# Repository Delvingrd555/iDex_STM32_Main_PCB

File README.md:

# iDex_STM32_Main_PCB
Main PCB Designs and Circuits Only

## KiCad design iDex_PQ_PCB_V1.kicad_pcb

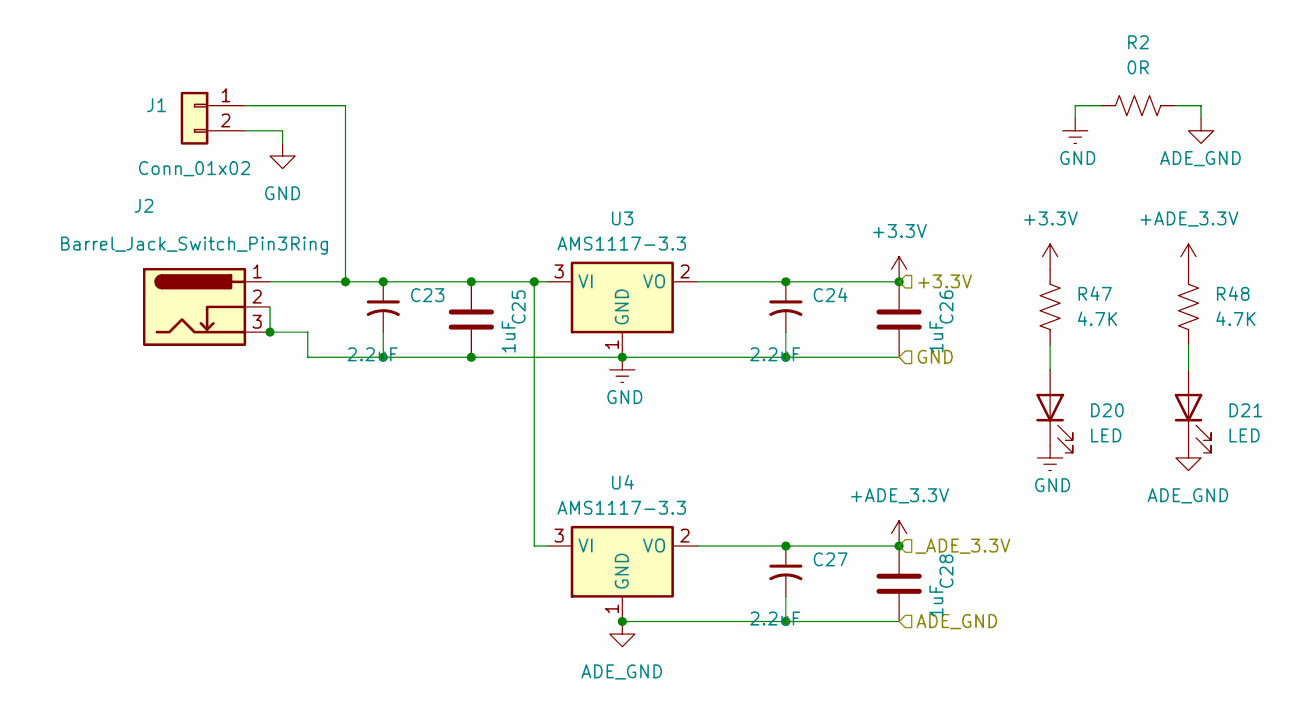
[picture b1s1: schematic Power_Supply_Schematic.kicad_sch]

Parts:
C23, C24, C27: 2.2uF; C_Radial_D10.0mm_H12.5mm_P5.00mm
C25, C26, C28: 1uF; C_1206_3216Metric_Pad1.33x1.80mm_HandSolder
D20, D21: LED; LED_0805_2012Metric_Pad1.15x1.40mm_HandSolder
J1: Conn_01x02; Altech_AK100_1x02_P5.00mm
J2: Barrel_Jack_Switch_Pin3Ring; BarrelJack_Horizontal
R2: 0R; R_0805_2012Metric_Pad1.20x1.40mm_HandSolder
R47, R48: 4.7K; R_0805_2012Metric_Pad1.20x1.40mm_HandSolder
U3, U4: AMS1117-3.3; SOT-223-3_TabPin2

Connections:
+3.3V: C24.1, C26.2, R47.2, U3.2 (VO); also elsewhere on the board
+ADE_3.3V: C27.1, C28.2, R48.2, U4.2 (VO); also elsewhere on the board
ADE_GND: C27.2, C28.1, D21.1 (K), R2.2, U4.1 (GND); also elsewhere on the board
GND: C23.2, C24.2, C25.1, C26.1, D20.1 (K), J1.2, J2.2, J2.3, R2.1, U3.1 (GND); also elsewhere on the board
unnamed: D20.2 (A), R47.1
unnamed: D21.2 (A), R48.1
unnamed: C23.1, C25.2, J1.1, J2.1, U3.3 (VI), U4.3 (VI)

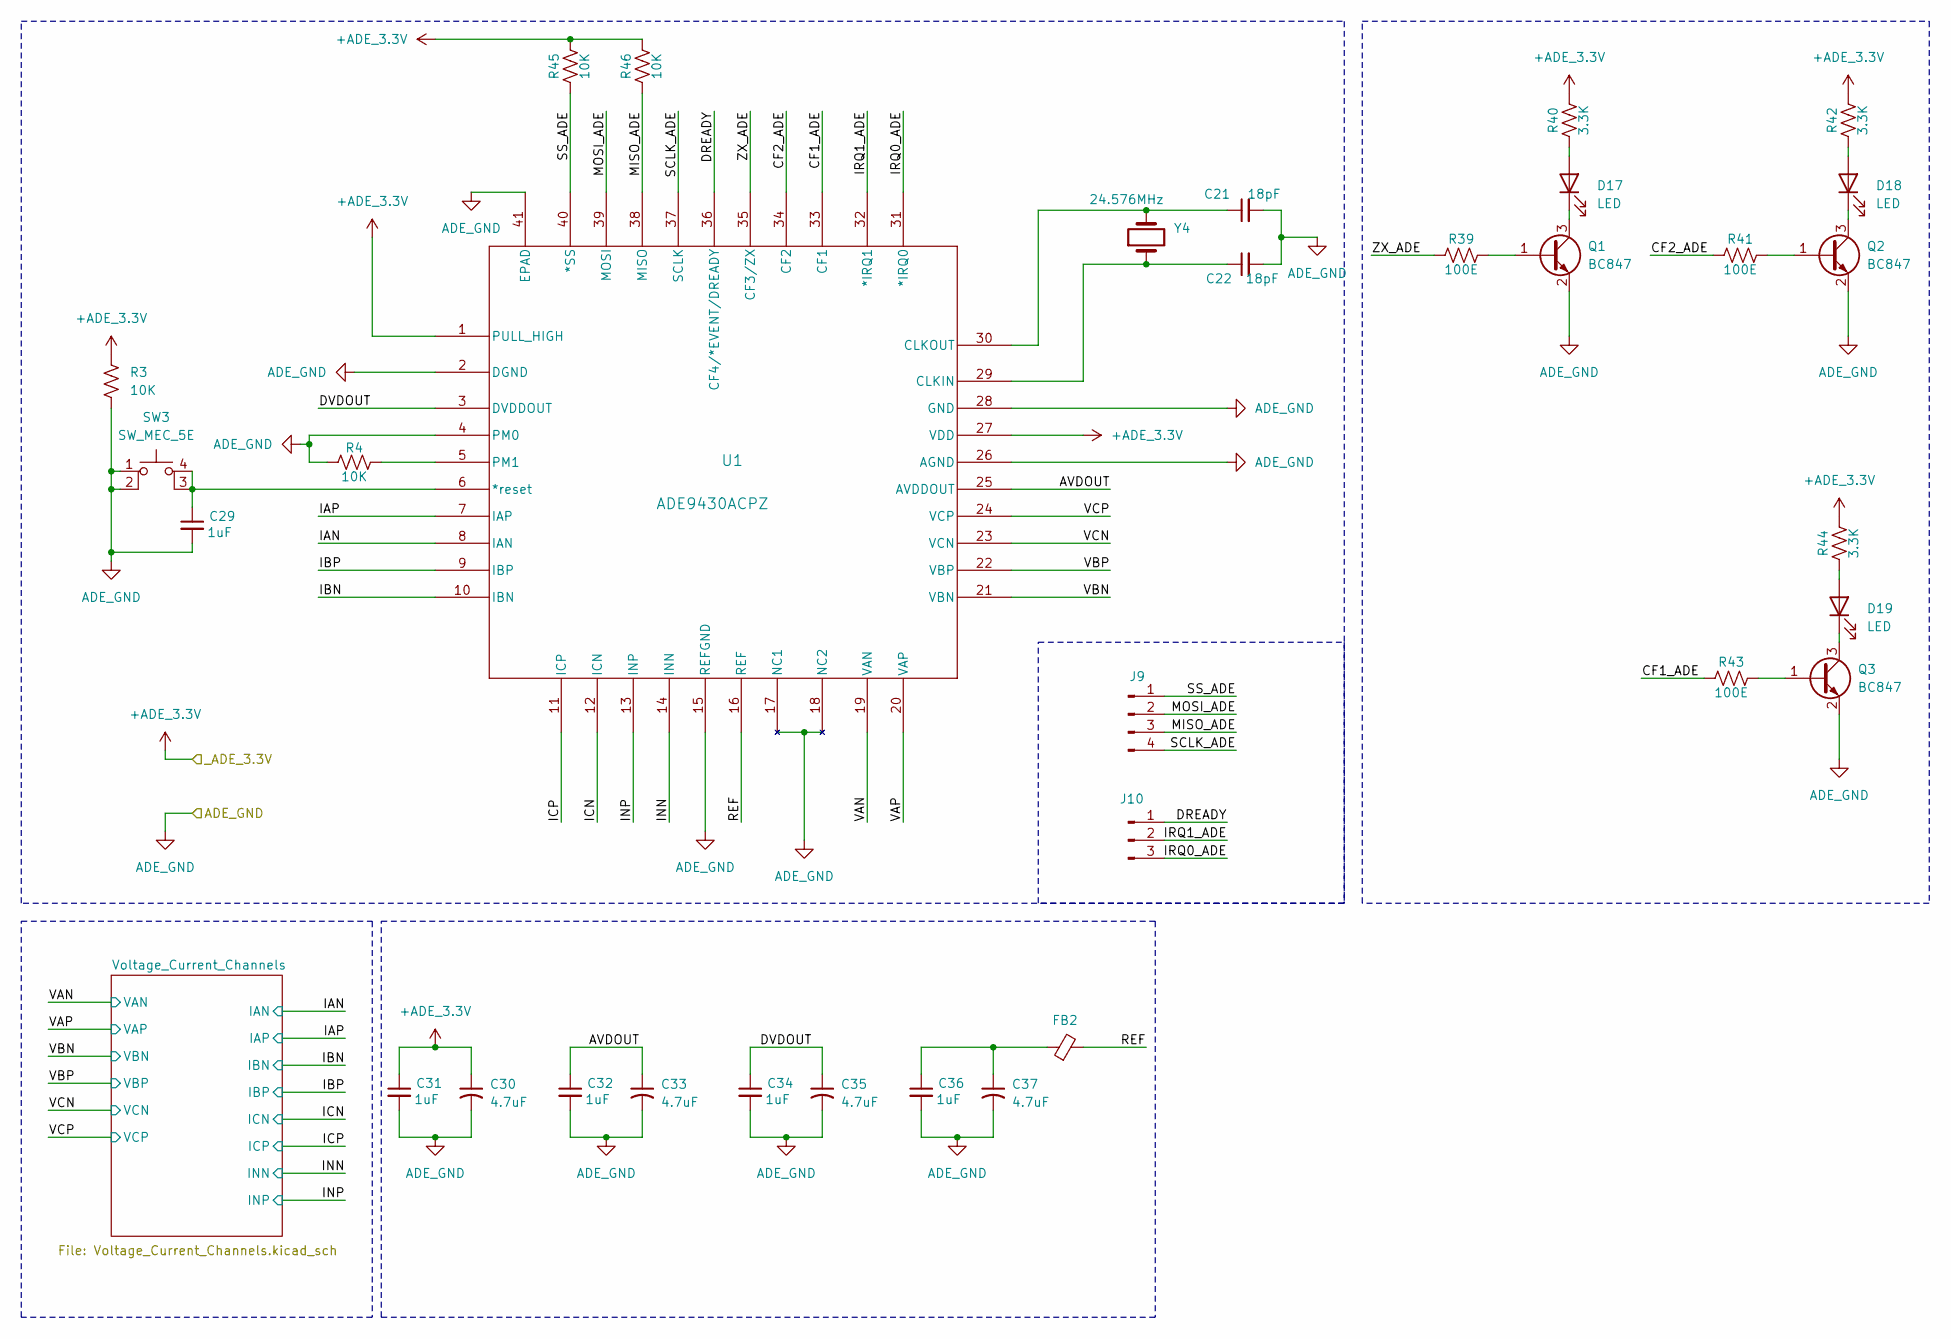
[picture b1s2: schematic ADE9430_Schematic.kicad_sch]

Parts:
C21, C22: 18pF; C_0805_2012Metric_Pad1.18x1.45mm_HandSolder
C29, C31, C32, C34, C36: 1uF; C_0805_2012Metric_Pad1.18x1.45mm_HandSolder
C30, C33, C35, C37: 4.7uF; C_Radial_D6.3mm_H5.0mm_P2.50mm
D17, D18, D19: LED; LED_D3.0mm
FB2: FerriteBead_Small; C_1206_3216Metric
J9: Conn; PinHeader_1x04_P2.54mm_Vertical
J10: Conn_01x03_Pin; PinHeader_1x03_P2.54mm_Vertical
Q1, Q2, Q3: BC847; SOT-23
R3, R4, R45, R46: 10K; R_0805_2012Metric_Pad1.20x1.40mm_HandSolder
R39, R41, R43: 100E; R_0805_2012Metric_Pad1.20x1.40mm_HandSolder
R40, R42, R44: 3.3K; R_0805_2012Metric_Pad1.20x1.40mm_HandSolder
SW3: SW_MEC_5E; SW_Push_2P1T_Toggle_CK_PVA1xxH1xxxxxxV2
U1: ADE9430ACPZ; ADE9430ACPZ_ADI
Y4: 24.576MHz; Crystal_HC50_Vertical

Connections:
+ADE_3.3V: C30.1, C31.1, R3.1, R40.2, R42.2, R44.2, R45.2, R46.2, U1.1 (PULL_HIGH), U1.27 (VDD); also elsewhere on the board
/ADE9430_Schematic/AVDOUT: C32.1, C33.1, U1.25 (AVDDOUT)
/ADE9430_Schematic/CF1_ADE: R43.1, U1.33 (CF1)
/ADE9430_Schematic/CF2_ADE: R41.1, U1.34 (CF2)
/ADE9430_Schematic/DREADY: J10.1, U1.36 (CF4/*EVENT/DREADY)
/ADE9430_Schematic/DVDOUT: C34.1, C35.1, U1.3 (DVDDOUT)
/ADE9430_Schematic/IAN: U1.8 (IAN); also elsewhere on the board
/ADE9430_Schematic/IAP: U1.7 (IAP); also elsewhere on the board
/ADE9430_Schematic/IBN: U1.10 (IBN); also elsewhere on the board
/ADE9430_Schematic/IBP: U1.9 (IBP); also elsewhere on the board
/ADE9430_Schematic/ICN: U1.12 (ICN); also elsewhere on the board
/ADE9430_Schematic/ICP: U1.11 (ICP); also elsewhere on the board
/ADE9430_Schematic/INN: U1.14 (INN); also elsewhere on the board
/ADE9430_Schematic/INP: U1.13 (INP); also elsewhere on the board
/ADE9430_Schematic/IRQ0_ADE: J10.3, U1.31 (*IRQ0)
/ADE9430_Schematic/IRQ1_ADE: J10.2, U1.32 (*IRQ1)
/ADE9430_Schematic/MISO_ADE: J9.3, R46.1, U1.38 (MISO)
/ADE9430_Schematic/MOSI_ADE: J9.2, U1.39 (MOSI)
/ADE9430_Schematic/REF: FB2.2, U1.16 (REF)
/ADE9430_Schematic/SCLK_ADE: J9.4, U1.37 (SCLK)
/ADE9430_Schematic/SS_ADE: J9.1, R45.1, U1.40 (*SS)
/ADE9430_Schematic/VAN: U1.19 (VAN); also elsewhere on the board
/ADE9430_Schematic/VAP: U1.20 (VAP); also elsewhere on the board
/ADE9430_Schematic/VBN: U1.21 (VBN); also elsewhere on the board
/ADE9430_Schematic/VBP: U1.22 (VBP); also elsewhere on the board
/ADE9430_Schematic/VCN: U1.23 (VCN); also elsewhere on the board
/ADE9430_Schematic/VCP: U1.24 (VCP); also elsewhere on the board
/ADE9430_Schematic/ZX_ADE: R39.1, U1.35 (CF3/ZX)
ADE_GND: C21.2, C22.2, C29.2, C30.2, C31.2, C32.2, C33.2, C34.2, C35.2, C36.2, C37.2, Q1.2 (E), Q2.2 (E), Q3.2 (E), R3.2, R4.1, SW3.1, SW3.2, U1.2 (DGND), U1.4 (PM0), U1.15 (REFGND), U1.17 (NC1), U1.18 (NC2), U1.26 (AGND), U1.28 (GND), U1.41 (EPAD); also elsewhere on the board
unnamed: C36.1, C37.1, FB2.1
unnamed: D17.2 (A), R40.1
unnamed: D17.1 (K), Q1.3 (C)
unnamed: D18.2 (A), R42.1
unnamed: D18.1 (K), Q2.3 (C)
unnamed: D19.2 (A), R44.1
unnamed: D19.1 (K), Q3.3 (C)
unnamed: Q1.1 (B), R39.2
unnamed: Q2.1 (B), R41.2
unnamed: Q3.1 (B), R43.2
unnamed: C29.1, SW3.3 (K), SW3.4 (A), U1.6 (*reset)
unnamed: C22.1, U1.29 (CLKIN), Y4.1
unnamed: C21.1, U1.30 (CLKOUT), Y4.2
unnamed: R4.2, U1.5 (PM1)

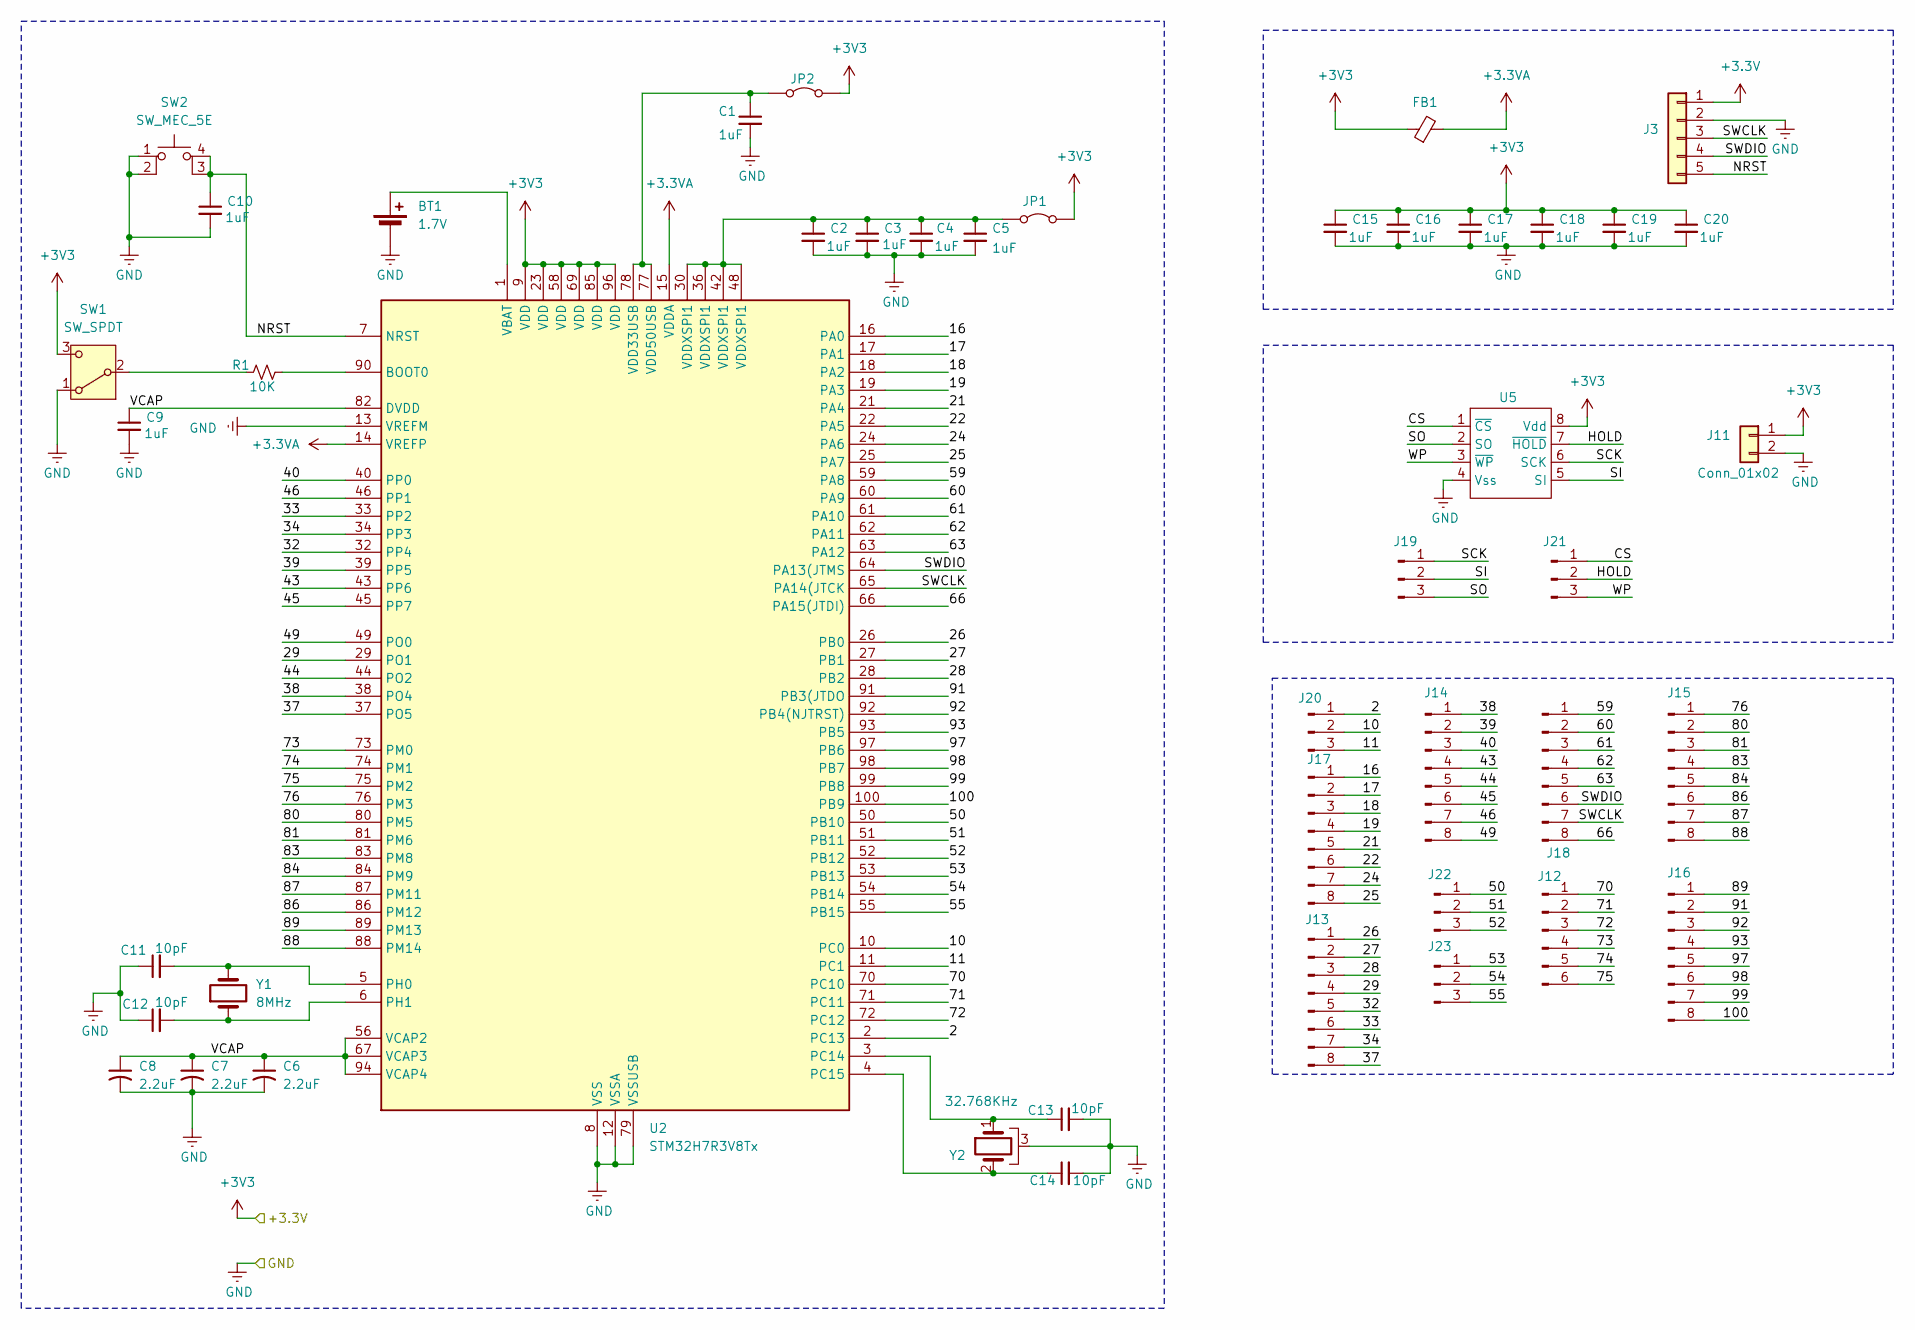
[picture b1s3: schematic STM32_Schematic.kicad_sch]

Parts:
BT1: 1.7V; BatteryHolder_MYOUNG_BS-07-A1BJ001_CR2032
C1, C2, C3, C4, C5, C9, C10, C15, C16, C17, C18, C19, C20: 1uF; C_0805_2012Metric_Pad1.18x1.45mm_HandSolder
C6, C7, C8: 2.2uF; C_Radial_D6.3mm_H5.0mm_P2.50mm
C11, C12, C13, C14: 10pF; C_0805_2012Metric_Pad1.18x1.45mm_HandSolder
FB1: FerriteBead_Small; C_1206_3216Metric
J3: Conn_01x05; TerminalBlock_Phoenix_MPT-0,5-5-2.54_1x05_P2.54mm_Horizontal
J11: Conn_01x02; PinSocket_1x02_P2.54mm_Vertical
J12: Conn_01x06_Pin; PinHeader_1x06_P2.54mm_Vertical
J13, J14, J15, J16, J17, J18: Conn_01x08_Pin; PinSocket_1x08_P2.54mm_Vertical
J19, J20, J21, J22, J23: Conn_01x03_Pin; PinHeader_1x03_P2.54mm_Vertical
JP1, JP2: Jumper_2_Bridged; PinHeader_1x02_P2.54mm_Vertical
R1: 10K; R_0805_2012Metric_Pad1.20x1.40mm_HandSolder
SW1: SW_SPDT; PinHeader_1x03_P2.54mm_Vertical
SW2: SW_MEC_5E; SW_Push_2P1T_Toggle_CK_PVA1xxH1xxxxxxV2
U2: STM32H7R3V8Tx; LQFP-100_14x14mm_P0.5mm
U5: SOIC-8_3.9x4.9mm_P1.27mm
Y1: 8MHz; Crystal_HC50_Vertical
Y2: 32.768KHz; Crystal_DS26_D2.0mm_L6.0mm_Horizontal_1EP_style1

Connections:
+3.3V: C15.1, C16.1, C17.1, C18.1, C19.1, C20.1, FB1.1, J3.1, J11.1, JP1.2 (B), JP2.2 (B), SW1.3 (C), U2.9 (VDD), U2.23 (VDD), U2.58 (VDD), U2.69 (VDD), U2.85 (VDD), U2.96 (VDD), U5.8 (Vdd); also elsewhere on the board
+3.3VA: FB1.2, U2.14 (VREFP), U2.15 (VDDA)
/STM32_Schematic/2: J20.1, U2.2 (PC13)
/STM32_Schematic/10: J20.2, U2.10 (PC0)
/STM32_Schematic/11: J20.3, U2.11 (PC1)
/STM32_Schematic/16: J17.1, U2.16 (PA0)
/STM32_Schematic/17: J17.2, U2.17 (PA1)
/STM32_Schematic/18: J17.3, U2.18 (PA2)
/STM32_Schematic/19: J17.4, U2.19 (PA3)
/STM32_Schematic/21: J17.5, U2.21 (PA4)
/STM32_Schematic/22: J17.6, U2.22 (PA5)
/STM32_Schematic/24: J17.7, U2.24 (PA6)
/STM32_Schematic/25: J17.8, U2.25 (PA7)
/STM32_Schematic/26: J13.1, U2.26 (PB0)
/STM32_Schematic/27: J13.2, U2.27 (PB1)
/STM32_Schematic/28: J13.3, U2.28 (PB2)
/STM32_Schematic/29: J13.4, U2.29 (PO1)
/STM32_Schematic/32: J13.5, U2.32 (PP4)
/STM32_Schematic/33: J13.6, U2.33 (PP2)
/STM32_Schematic/34: J13.7, U2.34 (PP3)
/STM32_Schematic/37: J13.8, U2.37 (PO5)
/STM32_Schematic/38: J14.1, U2.38 (PO4)
/STM32_Schematic/39: J14.2, U2.39 (PP5)
/STM32_Schematic/40: J14.3, U2.40 (PP0)
/STM32_Schematic/43: J14.4, U2.43 (PP6)
/STM32_Schematic/44: J14.5, U2.44 (PO2)
/STM32_Schematic/45: J14.6, U2.45 (PP7)
/STM32_Schematic/46: J14.7, U2.46 (PP1)
/STM32_Schematic/49: J14.8, U2.49 (PO0)
/STM32_Schematic/50: J22.1, U2.50 (PB10)
/STM32_Schematic/51: J22.2, U2.51 (PB11)
/STM32_Schematic/52: J22.3, U2.52 (PB12)
/STM32_Schematic/53: J23.1, U2.53 (PB13)
/STM32_Schematic/54: J23.2, U2.54 (PB14)
/STM32_Schematic/55: J23.3, U2.55 (PB15)
/STM32_Schematic/59: J18.1, U2.59 (PA8)
/STM32_Schematic/60: J18.2, U2.60 (PA9)
/STM32_Schematic/61: J18.3, U2.61 (PA10)
/STM32_Schematic/62: J18.4, U2.62 (PA11)
/STM32_Schematic/63: J18.5, U2.63 (PA12)
/STM32_Schematic/66: J18.8, U2.66 (PA15(JTDI))
/STM32_Schematic/70: J12.1, U2.70 (PC10)
/STM32_Schematic/71: J12.2, U2.71 (PC11)
/STM32_Schematic/72: J12.3, U2.72 (PC12)
/STM32_Schematic/73: J12.4, U2.73 (PM0)
/STM32_Schematic/74: J12.5, U2.74 (PM1)
/STM32_Schematic/75: J12.6, U2.75 (PM2)
/STM32_Schematic/76: J15.1, U2.76 (PM3)
/STM32_Schematic/80: J15.2, U2.80 (PM5)
/STM32_Schematic/81: J15.3, U2.81 (PM6)
/STM32_Schematic/83: J15.4, U2.83 (PM8)
/STM32_Schematic/84: J15.5, U2.84 (PM9)
/STM32_Schematic/86: J15.6, U2.86 (PM12)
/STM32_Schematic/87: J15.7, U2.87 (PM11)
/STM32_Schematic/88: J15.8, U2.88 (PM14)
/STM32_Schematic/89: J16.1, U2.89 (PM13)
/STM32_Schematic/91: J16.2, U2.91 (PB3(JTDO)
/STM32_Schematic/92: J16.3, U2.92 (PB4(NJTRST))
/STM32_Schematic/93: J16.4, U2.93 (PB5)
/STM32_Schematic/97: J16.5, U2.97 (PB6)
/STM32_Schematic/98: J16.6, U2.98 (PB7)
/STM32_Schematic/99: J16.7, U2.99 (PB8)
/STM32_Schematic/100: J16.8, U2.100 (PB9)
/STM32_Schematic/CS: J21.1, U5.1 (~CS)
/STM32_Schematic/HOLD: J21.2, U5.7 (~HOLD)
/STM32_Schematic/NRST: C10.1, J3.5, SW2.3 (K), SW2.4 (A), U2.7 (NRST)
/STM32_Schematic/SCK: J19.1, U5.6 (SCK)
/STM32_Schematic/SI: J19.2, U5.5 (SI)
/STM32_Schematic/SO: J19.3, U5.2 (SO)
/STM32_Schematic/SWCLK: J3.3, J18.7, U2.65 (PA14(JTCK)
/STM32_Schematic/SWDIO: J3.4, J18.6, U2.64 (PA13(JTMS)
/STM32_Schematic/VCAP: C6.1, C7.1, C8.1, C9.1, U2.56 (VCAP2), U2.67 (VCAP3), U2.82 (DVDD), U2.94 (VCAP4)
/STM32_Schematic/WP: J21.3, U5.3 (~WP)
GND: BT1.2 (-), C1.2, C2.2, C3.2, C4.2, C5.2, C6.2, C7.2, C8.2, C9.2, C10.2, C11.1, C12.1, C13.2, C14.2, C15.2, C16.2, C17.2, C18.2, C19.2, C20.2, J3.2, J11.2, SW1.1 (A), SW2.1, SW2.2, U2.8 (VSS), U2.12 (VSSA), U2.13 (VREFM), U2.20 (VSS), U2.31 (VSS), U2.35 (VSS), U2.41 (VSS), U2.47 (VSS), U2.57 (VSS), U2.68 (VSS), U2.79 (VSSUSB), U2.95 (VSS), U5.4 (Vss), Y2.3; also elsewhere on the board
unnamed: BT1.1 (+), U2.1 (VBAT)
unnamed: C2.1, C3.1, C4.1, C5.1, JP1.1 (A), U2.30 (VDDXSPI1), U2.36 (VDDXSPI1), U2.42 (VDDXSPI1), U2.48 (VDDXSPI1)
unnamed: C1.1, JP2.1 (A), U2.77 (VDD50USB), U2.78 (VDD33USB)
unnamed: R1.1, SW1.2 (B)
unnamed: R1.2, U2.90 (BOOT0)
unnamed: C13.1, U2.3 (PC14), Y2.1
unnamed: C14.1, U2.4 (PC15), Y2.2
unnamed: C11.2, U2.5 (PH0), Y1.2
unnamed: C12.2, U2.6 (PH1), Y1.1

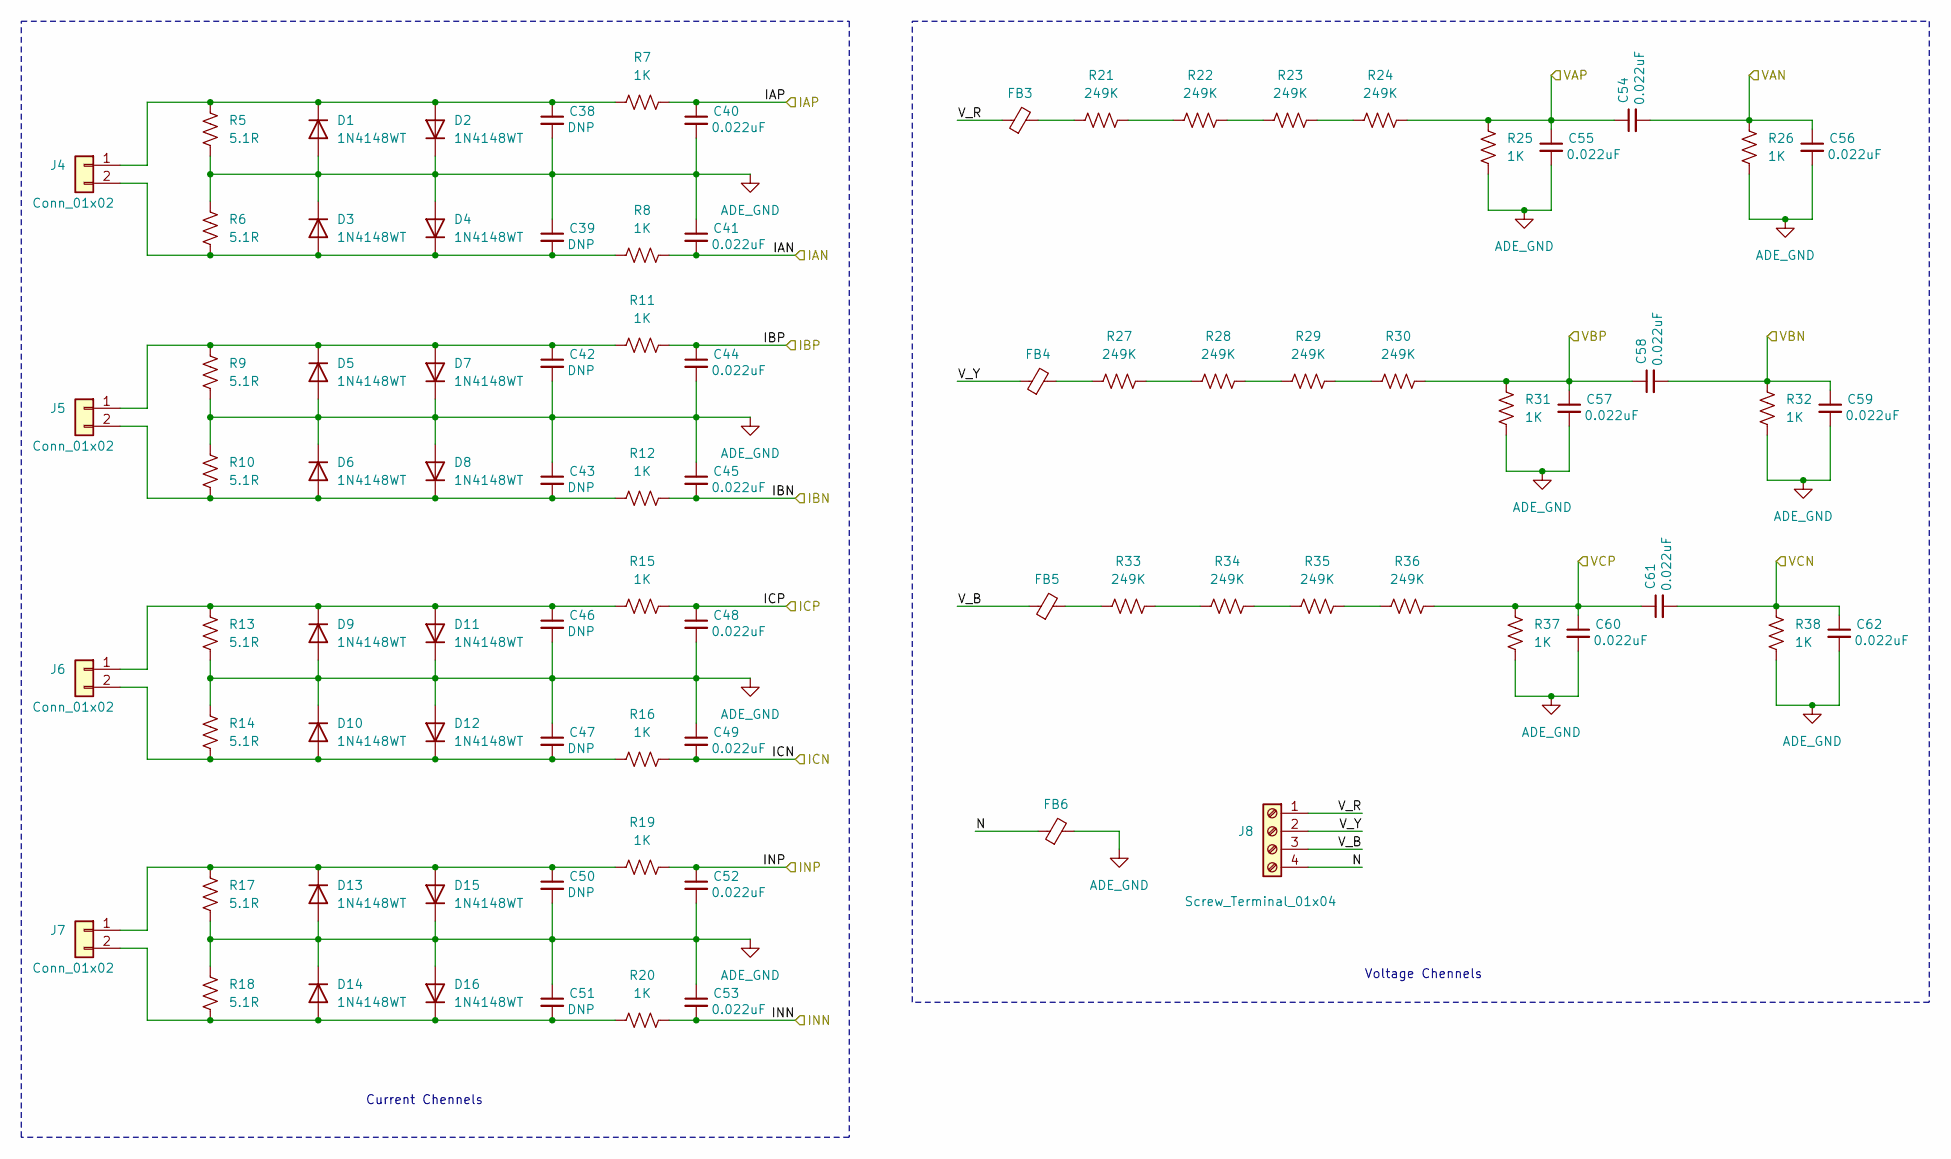
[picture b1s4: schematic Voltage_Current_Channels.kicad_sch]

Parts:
C38, C39, C42, C43, C46, C47, C50, C51: DNP; C_0805_2012Metric_Pad1.18x1.45mm_HandSolder
C40, C41, C44, C45, C48, C49, C52, C53, C54, C55, C56, C57, C58, C59, C60, C61, C62: 0.022uF; C_0805_2012Metric_Pad1.18x1.45mm_HandSolder
D1, D2, D3, D4, D5, D6, D7, D8, D9, D10, D11, D12, D13, D14, D15, D16: 1N4148WT; D_SOD-523
FB3, FB4, FB5, FB6: FerriteBead_Small; C_1206_3216Metric
J4, J5, J6, J7: Conn_01x02; PinSocket_1x02_P2.54mm_Vertical
J8: Screw_Terminal_01x04; TerminalBlock_MaiXu_MX126-5.0-04P_1x04_P5.00mm
R5, R6, R9, R10, R13, R14, R17, R18: 5.1R; R_0805_2012Metric_Pad1.20x1.40mm_HandSolder
R7, R8, R11, R12, R15, R16, R19, R20, R25, R26, R31, R32, R37, R38: 1K; R_0805_2012Metric_Pad1.20x1.40mm_HandSolder
R21, R22, R23, R24, R27, R28, R29, R30, R33, R34, R35, R36: 249K; R_0805_2012Metric_Pad1.20x1.40mm_HandSolder

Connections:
/ADE9430_Schematic/IAN: C41.2, R8.2; also elsewhere on the board
/ADE9430_Schematic/IAP: C40.1, R7.2; also elsewhere on the board
/ADE9430_Schematic/IBN: C45.2, R12.2; also elsewhere on the board
/ADE9430_Schematic/IBP: C44.1, R11.2; also elsewhere on the board
/ADE9430_Schematic/ICN: C49.2, R16.2; also elsewhere on the board
/ADE9430_Schematic/ICP: C48.1, R15.2; also elsewhere on the board
/ADE9430_Schematic/INN: C53.2, R20.2; also elsewhere on the board
/ADE9430_Schematic/INP: C52.1, R19.2; also elsewhere on the board
/ADE9430_Schematic/VAN: C54.2, C56.1, R26.2; also elsewhere on the board
/ADE9430_Schematic/VAP: C54.1, C55.1, R24.2, R25.2; also elsewhere on the board
/ADE9430_Schematic/VBN: C58.2, C59.1, R32.2; also elsewhere on the board
/ADE9430_Schematic/VBP: C57.1, C58.1, R30.2, R31.2; also elsewhere on the board
/ADE9430_Schematic/VCN: C61.2, C62.1, R38.2; also elsewhere on the board
/ADE9430_Schematic/VCP: C60.1, C61.1, R36.2, R37.2; also elsewhere on the board
/ADE9430_Schematic/Voltage_Current_Channels/N: FB6.1, J8.4
/ADE9430_Schematic/Voltage_Current_Channels/V_B: FB5.1, J8.3
/ADE9430_Schematic/Voltage_Current_Channels/V_R: FB3.1, J8.1
/ADE9430_Schematic/Voltage_Current_Channels/V_Y: FB4.1, J8.2
ADE_GND: C38.2, C39.1, C40.2, C41.1, C42.2, C43.1, C44.2, C45.1, C46.2, C47.1, C48.2, C49.1, C50.2, C51.1, C52.2, C53.1, C55.2, C56.2, C57.2, C59.2, C60.2, C62.2, D1.2 (A), D2.1 (K), D3.1 (K), D4.2 (A), D5.2 (A), D6.1 (K), D7.1 (K), D8.2 (A), D9.2 (A), D10.1 (K), D11.1 (K), D12.2 (A), D13.2 (A), D14.1 (K), D15.1 (K), D16.2 (A), FB6.2, R5.2, R6.1, R9.2, R10.1, R13.2, R14.1, R17.2, R18.1, R25.1, R26.1, R31.1, R32.1, R37.1, R38.1; also elsewhere on the board
unnamed: C38.1, D1.1 (K), D2.2 (A), J4.1, R5.1, R7.1
unnamed: C39.2, D3.2 (A), D4.1 (K), J4.2, R6.2, R8.1
unnamed: C42.1, D5.1 (K), D7.2 (A), J5.1, R9.1, R11.1
unnamed: C43.2, D6.2 (A), D8.1 (K), J5.2, R10.2, R12.1
unnamed: C47.2, D10.2 (A), D12.1 (K), J6.2, R14.2, R16.1
unnamed: C46.1, D9.1 (K), D11.2 (A), J6.1, R13.1, R15.1
unnamed: C50.1, D13.1 (K), D15.2 (A), J7.1, R17.1, R19.1
unnamed: C51.2, D14.2 (A), D16.1 (K), J7.2, R18.2, R20.1
unnamed: FB3.2, R21.1
unnamed: FB4.2, R27.1
unnamed: FB5.2, R33.1
unnamed: R21.2, R22.1
unnamed: R22.2, R23.1
unnamed: R23.2, R24.1
unnamed: R27.2, R28.1
unnamed: R28.2, R29.1
unnamed: R29.2, R30.1
unnamed: R33.2, R34.1
unnamed: R34.2, R35.1
unnamed: R35.2, R36.1

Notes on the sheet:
Voltage Chennels
Current Chennels

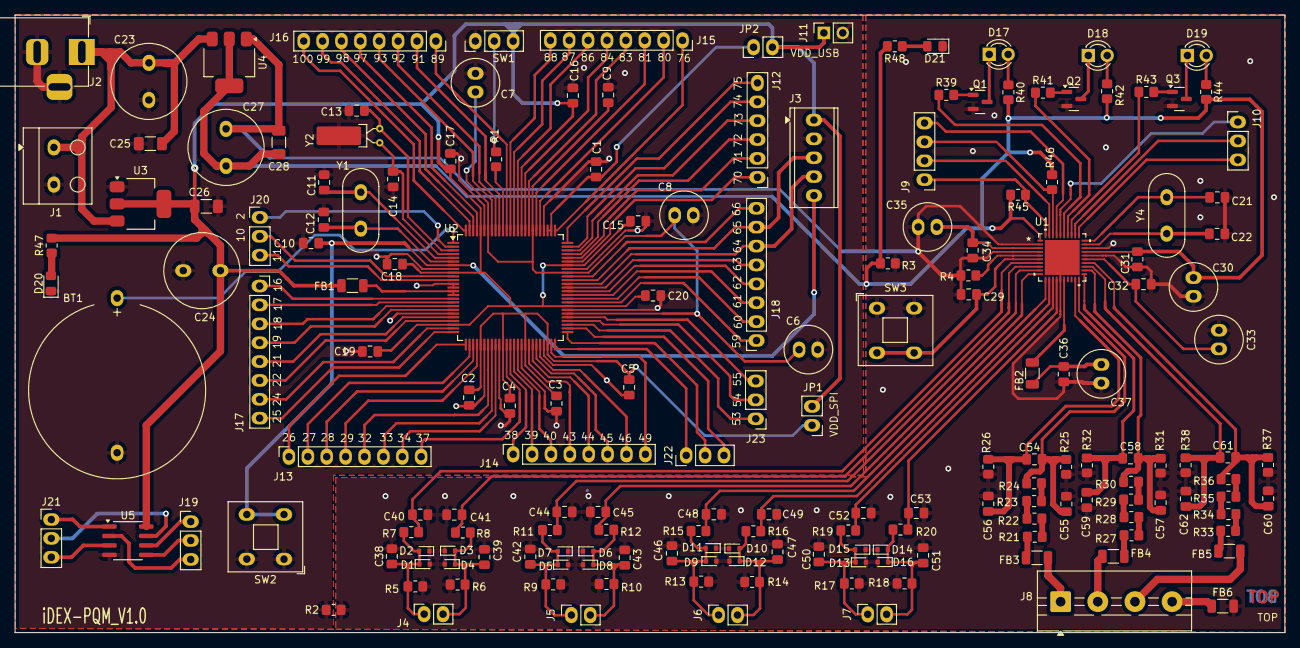
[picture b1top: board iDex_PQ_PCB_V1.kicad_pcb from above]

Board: 2 copper layers, 170.8 x 83.1 mm, 177 parts (0 on the bottom side), 153 nets.

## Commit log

2025-08-27 Complete PCB
2025-08-27 Bottom Layer Plane Added
2025-08-27 Changes done as per Poineer Circuits
2025-08-27 Voltage Foot print changed
2025-08-27 voltage foot print 2
2025-08-28 track width changed
2025-08-28 Kumaravel
